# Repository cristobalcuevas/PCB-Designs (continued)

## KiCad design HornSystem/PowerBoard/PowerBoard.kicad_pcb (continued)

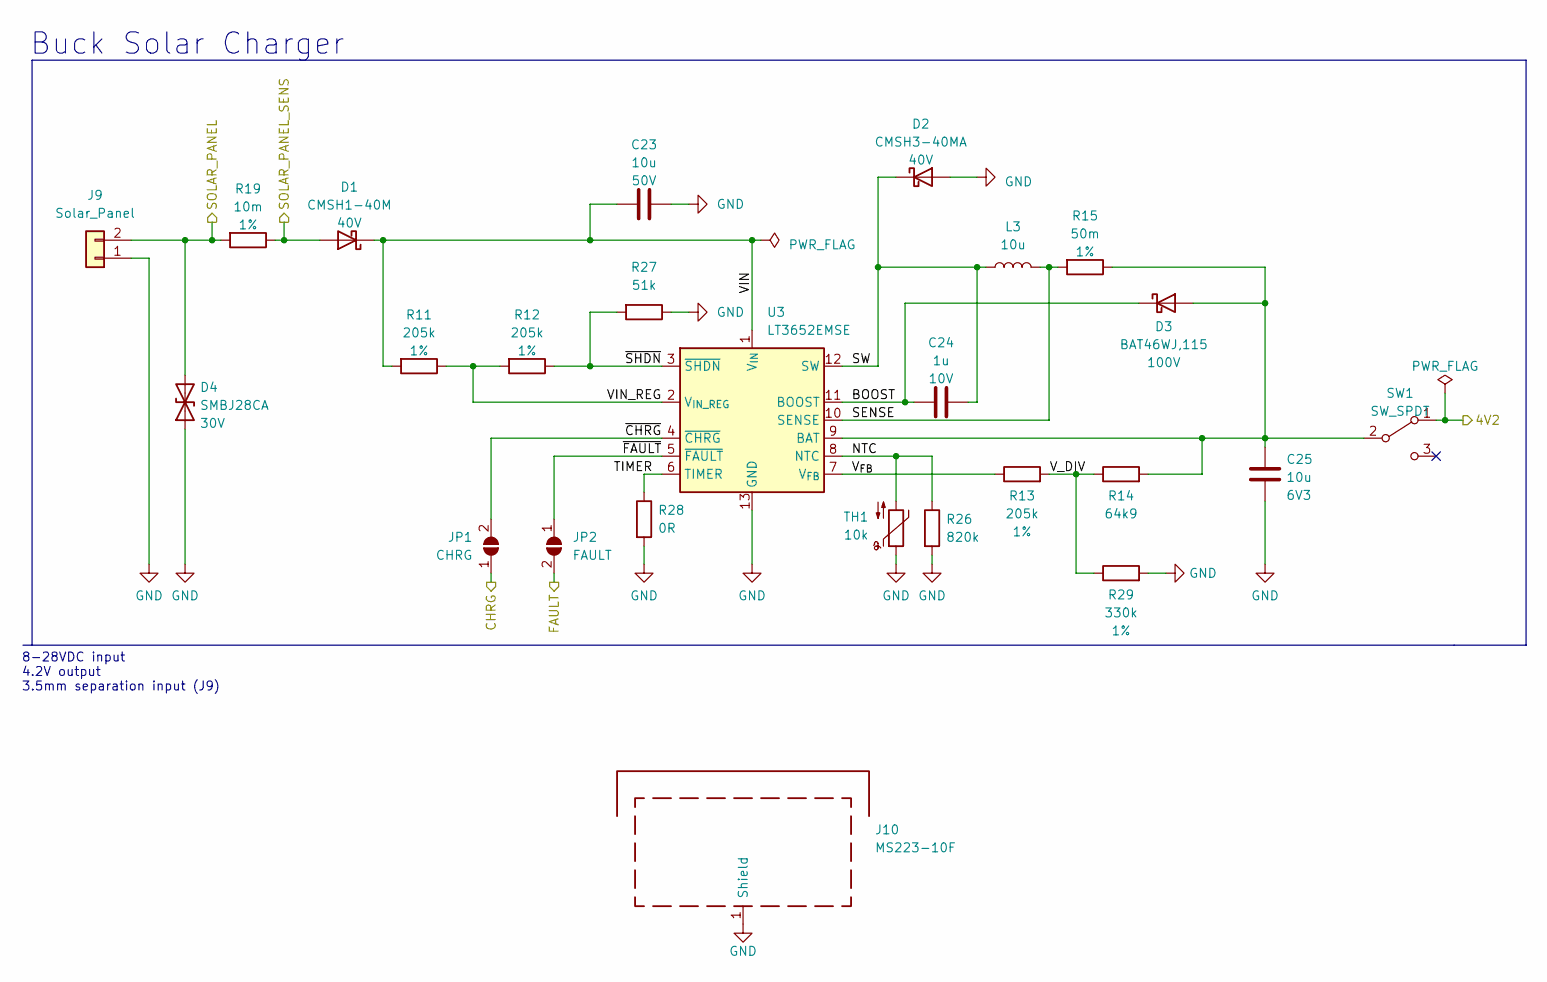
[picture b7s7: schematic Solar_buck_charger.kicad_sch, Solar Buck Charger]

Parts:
C23: 10u; C_0805_2012Metric; Voltage 50V; JLCPCB Part C440198
C24: 1u; C_0805_2012Metric; Voltage 10V; JLCPCB Part C440195
C25: 10u; C_0805_2012Metric; Voltage 6V3; JLCPCB Part C380333
D1: CMSH1-40M; D_SMA; Voltage 40V; JLCPCB Part C15759
D2: CMSH3-40MA; D_SMA; Voltage 40V; JLCPCB Part C85098
D3: BAT46WJ,115; D_SOD-323F; Voltage 100V; JLCPCB Part C114696
D4: SMBJ28CA; D_SMB; Voltage 30V; JLCPCB Part C353369
J9: Solar_Panel; TerminalBlock_Phoenix_PT-1,5-2-3.5-H_1x02_P3.50mm_Horizontal; JLCPCB Part C474892
J10: MS223-10F; Wuerth_36103255_25x25mm; Digikey Part 732-2489-ND
JP1: CHRG; SolderJumper-2_P1.3mm_Open_RoundedPad1.0x1.5mm
JP2: FAULT; SolderJumper-2_P1.3mm_Open_RoundedPad1.0x1.5mm
L3: 10u; L_Vishay_IHLP-2525; JLCPCB Part C845015
R11, R12, R13: 205k; R_0805_2012Metric; Tolerance 1%; JLCPCB Part C322347
R14: 64k9; R_0805_2012Metric; JLCPCB Part C101826
R15: 50m; R_0805_2012Metric; Tolerance 1%; JLCPCB Part C270863
R19: 10m; R_0805_2012Metric; Tolerance 1%; JLCPCB Part C473034
R26: 820k; R_0805_2012Metric; JLCPCB Part C416171
R27: 51k; R_0805_2012Metric; Tolerance 1%; JLCPCB Part C17737
R28: 0R; R_0805_2012Metric; JLCPCB Part C2907288
R29: 330k; R_0805_2012Metric; Tolerance 1%; JLCPCB Part C104230
SW1: SW_SPDT; SW_SPDT_PCM12; JLCPCB Part C221841
TH1: 10k; PinHeader_1x02_P2.54mm_Vertical
U3: LT3652EMSE; MSOP-12-1EP_3x4mm_P0.65mm_EP1.65x2.85mm; JLCPCB Part C671115

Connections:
/4V2: SW1.1 (A); also elsewhere on the board
/INA Measurements/SOLAR_PANEL: D4.2 (A2), J9.2, R19.2; also elsewhere on the board
/INA Measurements/SOLAR_PANEL_SENS: D1.2 (A), R19.1; also elsewhere on the board
/PCI Connector/CHRG: JP1.1 (A); also elsewhere on the board
/PCI Connector/FAULT: JP2.2 (B); also elsewhere on the board
/Solar Buck Charger/BOOST: C24.1, D3.1 (K), U3.11 (BOOST)
/Solar Buck Charger/NTC: R26.1, TH1.2, U3.8 (NTC)
/Solar Buck Charger/SENSE: L3.2, R15.2, U3.10 (SENSE)
/Solar Buck Charger/SW: C24.2, D2.1 (K), L3.1, U3.12 (SW)
/Solar Buck Charger/TIMER: R28.1, U3.6 (TIMER)
/Solar Buck Charger/VIN: C23.1, D1.1 (K), R11.2, U3.1 (V_{IN})
/Solar Buck Charger/VIN_REG: R11.1, R12.2, U3.2 (V_{IN_REG})
/Solar Buck Charger/V_DIV: R13.2, R14.1, R29.1
/Solar Buck Charger/V_{FB}: R13.1, U3.7 (V_{FB})
/Solar Buck Charger/~CHRG: JP1.2 (B), U3.4 (~CHRG)
/Solar Buck Charger/~FAULT: JP2.1 (A), U3.5 (~FAULT)
/Solar Buck Charger/~SHDN: R12.1, R27.2, U3.3 (~SHDN)
GND: C23.2, C25.2, D2.2 (A), D4.1 (A1), J9.1, J10.1 (Shield), R26.2, R27.1, R28.2, R29.2, TH1.1, U3.13 (GND); also elsewhere on the board
unnamed: C25.1, D3.2 (A), R14.2, R15.1, SW1.2 (B), U3.9 (BAT)

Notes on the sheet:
8-28VDC input 4.2V output 3.5mm separation input (J9)
Buck Solar Charger

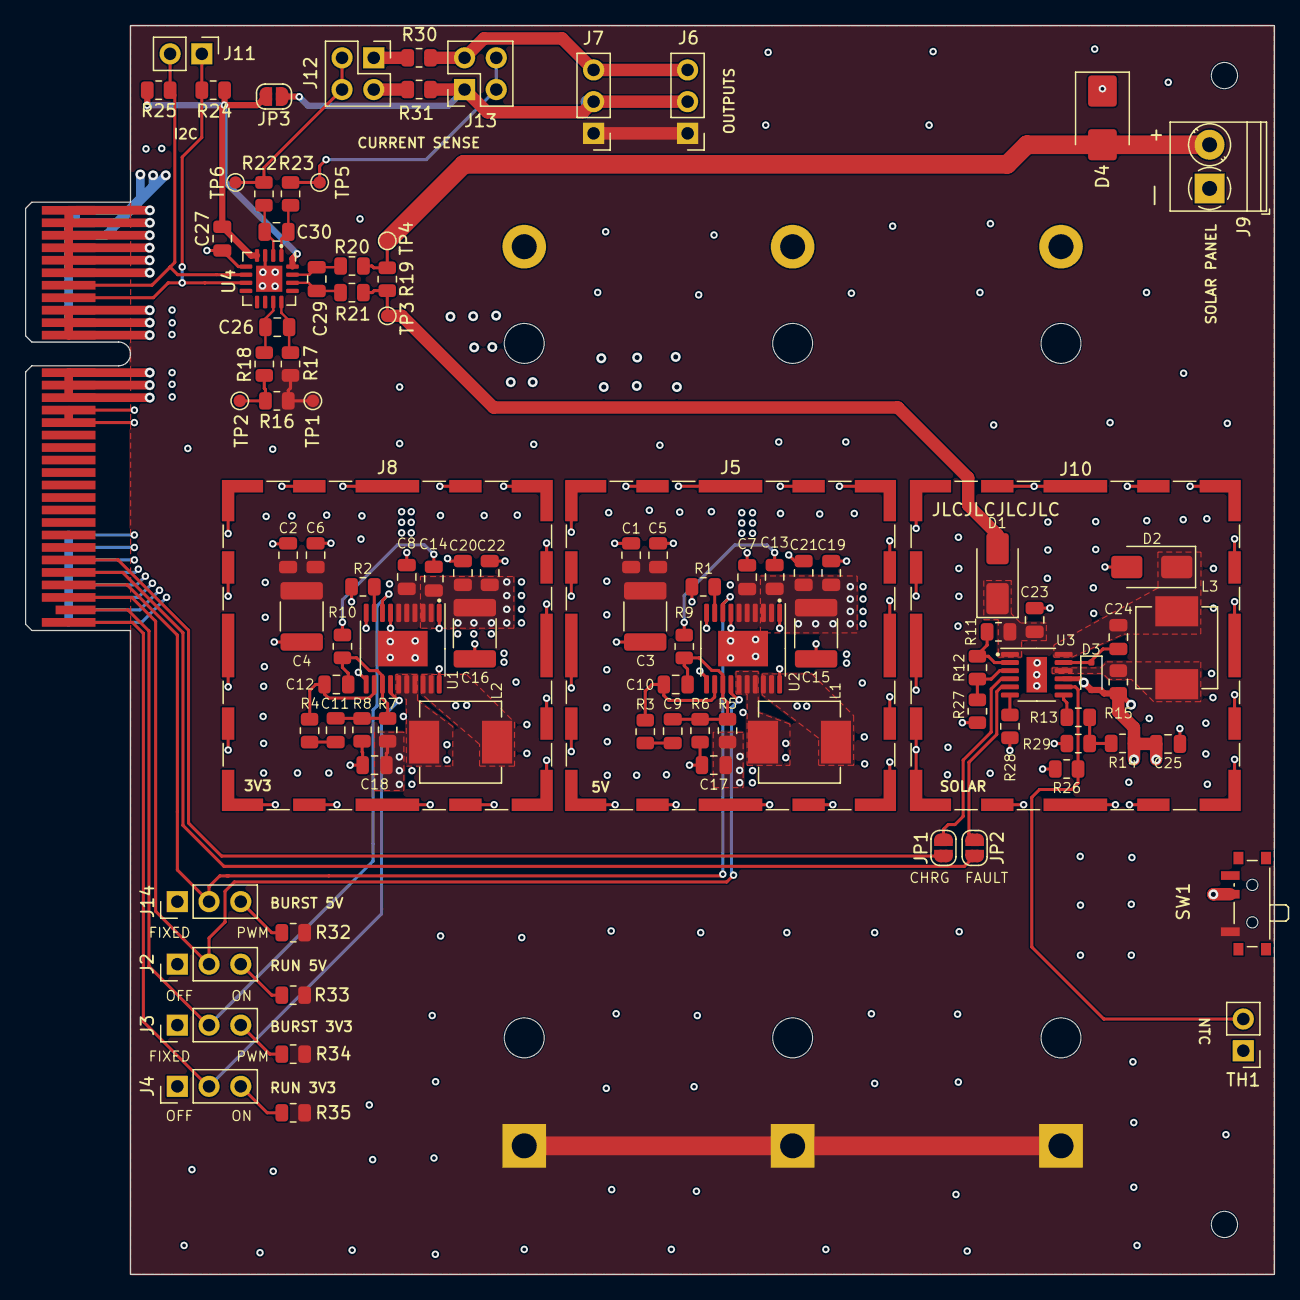
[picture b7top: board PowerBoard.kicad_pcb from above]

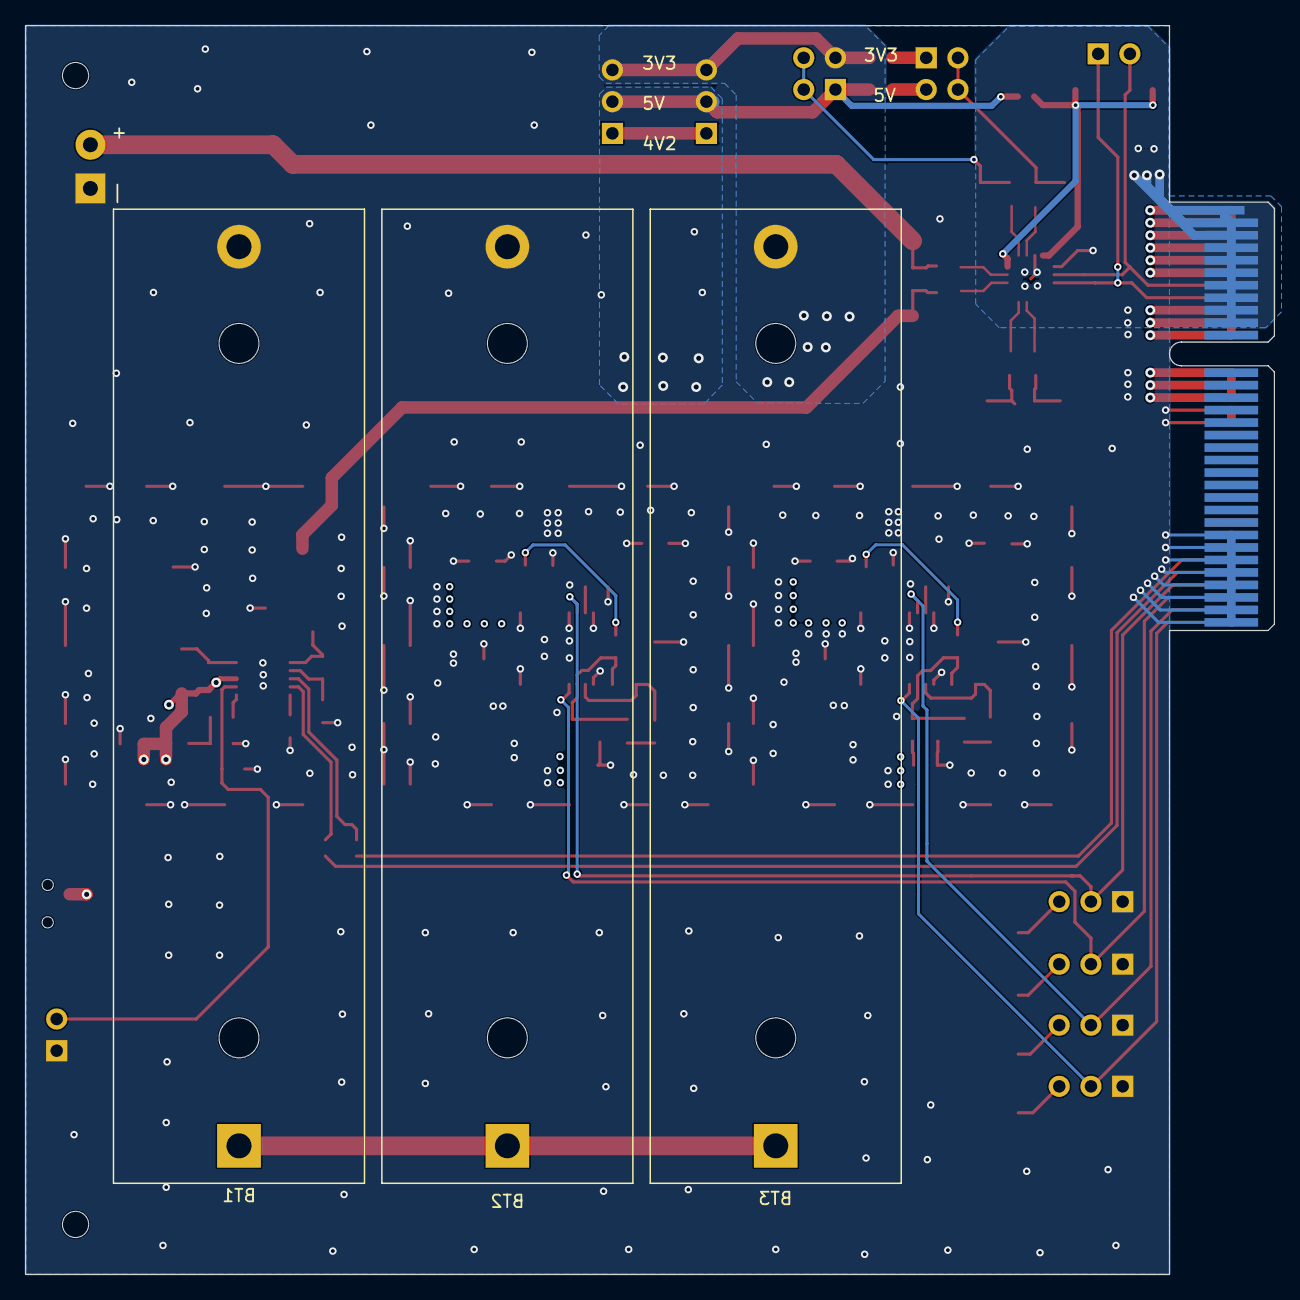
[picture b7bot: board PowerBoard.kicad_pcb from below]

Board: 4 copper layers, 100.0 x 100.0 mm, 105 parts (3 on the bottom side), 57 nets.

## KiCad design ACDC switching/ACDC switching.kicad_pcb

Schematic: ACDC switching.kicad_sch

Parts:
C1: 2.2u@1kV; C_Disc_D10.5mm_W5.0mm_P5.00mm
C2: 47u@400V; CP_Radial_D10.0mm_P5.00mm
C3, C4: 1000u@10V; CP_Radial_D12.5mm_P5.00mm
C5: 100u@35V; CP_Radial_D10.0mm_P5.00mm
C6: 0.1uF/50V; C_Rect_L7.2mm_W3.5mm_P5.00mm_FKS2_FKP2_MKS2_MKP2
D1: DF04M; Diode_Bridge_DIP-4_W7.62mm_P5.08mm
D2: LED; LED_D3.0mm
D3: 1N5822; D_DO-201AD_P15.24mm_Horizontal
D4: 1N4005; D_DO-15_P12.70mm_Horizontal
D5: 1N4148; D_DO-34_SOD68_P7.62mm_Horizontal
D6: 3V9; D_DO-41_SOD81_P10.16mm_Horizontal
Hm1, Hm2, Hm3, Hm4: MountingHole; MountingHole_3.2mm_M3
J1, J3: AC
J2: DC_OUT; Molex_KK-254_AE-6410-02A_1x02_P2.54mm_Vertical
J4: 12VDC; TestPoint_Pad_D1.0mm
J5: 0VDC; TestPoint_Pad_D1.0mm
L1: 10u@3A; L_Toroid_Vertical_L21.6mm_W9.1mm_P8.40mm_Bourns_5700
R1: 100k; R_Axial_DIN0207_L6.3mm_D2.5mm_P10.16mm_Horizontal
R2: 200k; R_Axial_DIN0207_L6.3mm_D2.5mm_P10.16mm_Horizontal
R3, R4: 1M; R_Axial_DIN0207_L6.3mm_D2.5mm_P10.16mm_Horizontal
R5: 59R; R_Axial_DIN0207_L6.3mm_D2.5mm_P10.16mm_Horizontal
R6: 10k; R_Axial_DIN0207_L6.3mm_D2.5mm_P10.16mm_Horizontal
R7: 680R; R_Axial_DIN0207_L6.3mm_D2.5mm_P10.16mm_Horizontal
T1: EE22; Transformer_Myrra_EF20_7408x
U1: TNY267P; PowerIntegrations_PDIP-8B
U2: PC817; DIP-4_W7.62mm

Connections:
GND: C2.2, C5.2, C6.2, D1.2 (-), J5.1, T1.5 (SA), U1.2 (S), U1.3 (S), U1.7 (S), U1.8 (S), U2.4
unnamed: C1.1, C2.1, D1.1 (+), R2.2, R3.2, T1.1 (SD)
unnamed: C1.2, D4.2 (A), R2.1
unnamed: C3.1, D3.1 (K), D6.1 (K), L1.1
unnamed: C3.2, C4.2, J2.1, R7.1, T1.8 (AA), U2.1
unnamed: C4.1, J2.2, L1.2
unnamed: C5.1, D5.1 (K), J4.1, R6.2
unnamed: C6.1, R6.1, U1.1 (BP)
unnamed: D1.3, J1.1, R1.2
unnamed: D1.4, D2.1 (K), J3.1
unnamed: D2.2 (A), R1.1
unnamed: D3.2 (A), T1.10 (AB)
unnamed: D4.1 (K), T1.2 (SC), U1.5 (D)
unnamed: D5.2 (A), T1.4 (SB)
unnamed: D6.2 (A), R5.2
unnamed: R3.1, R4.2
unnamed: R4.1, U1.4 (EN/UV), U2.3
unnamed: R5.1, R7.2, U2.2

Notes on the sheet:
https://www.youtube.com/watch?v=z1tEdvNH_xk

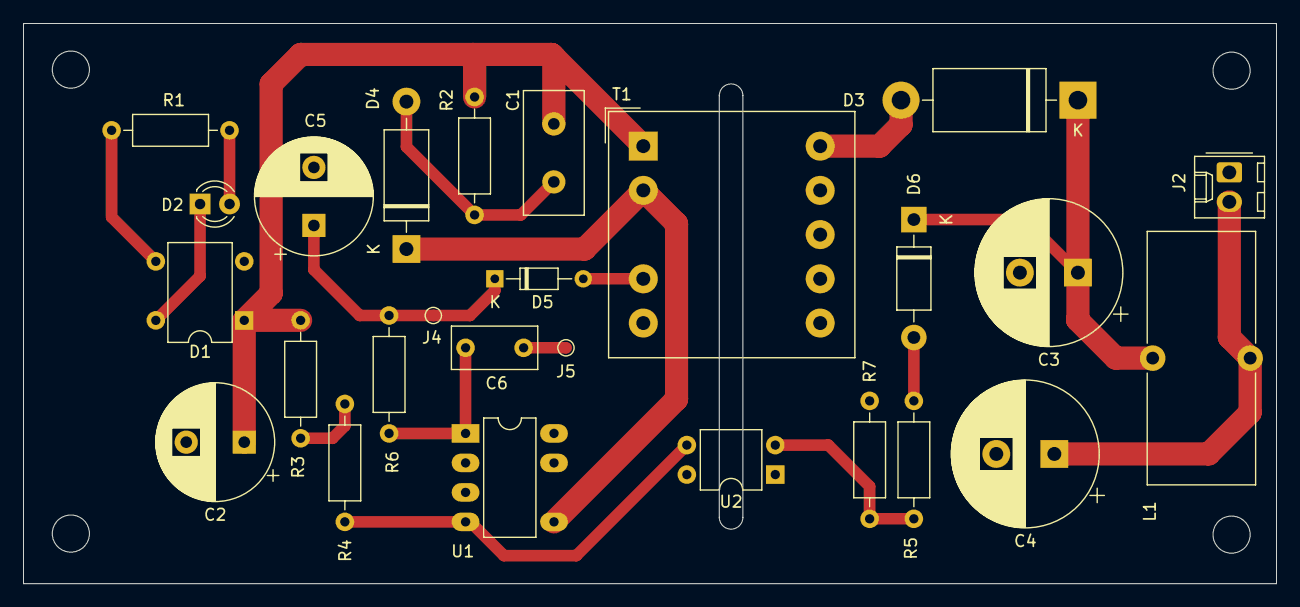
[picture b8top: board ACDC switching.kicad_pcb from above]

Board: 2 copper layers, 108.0 x 48.3 mm, 30 parts (0 on the bottom side), 18 nets.
